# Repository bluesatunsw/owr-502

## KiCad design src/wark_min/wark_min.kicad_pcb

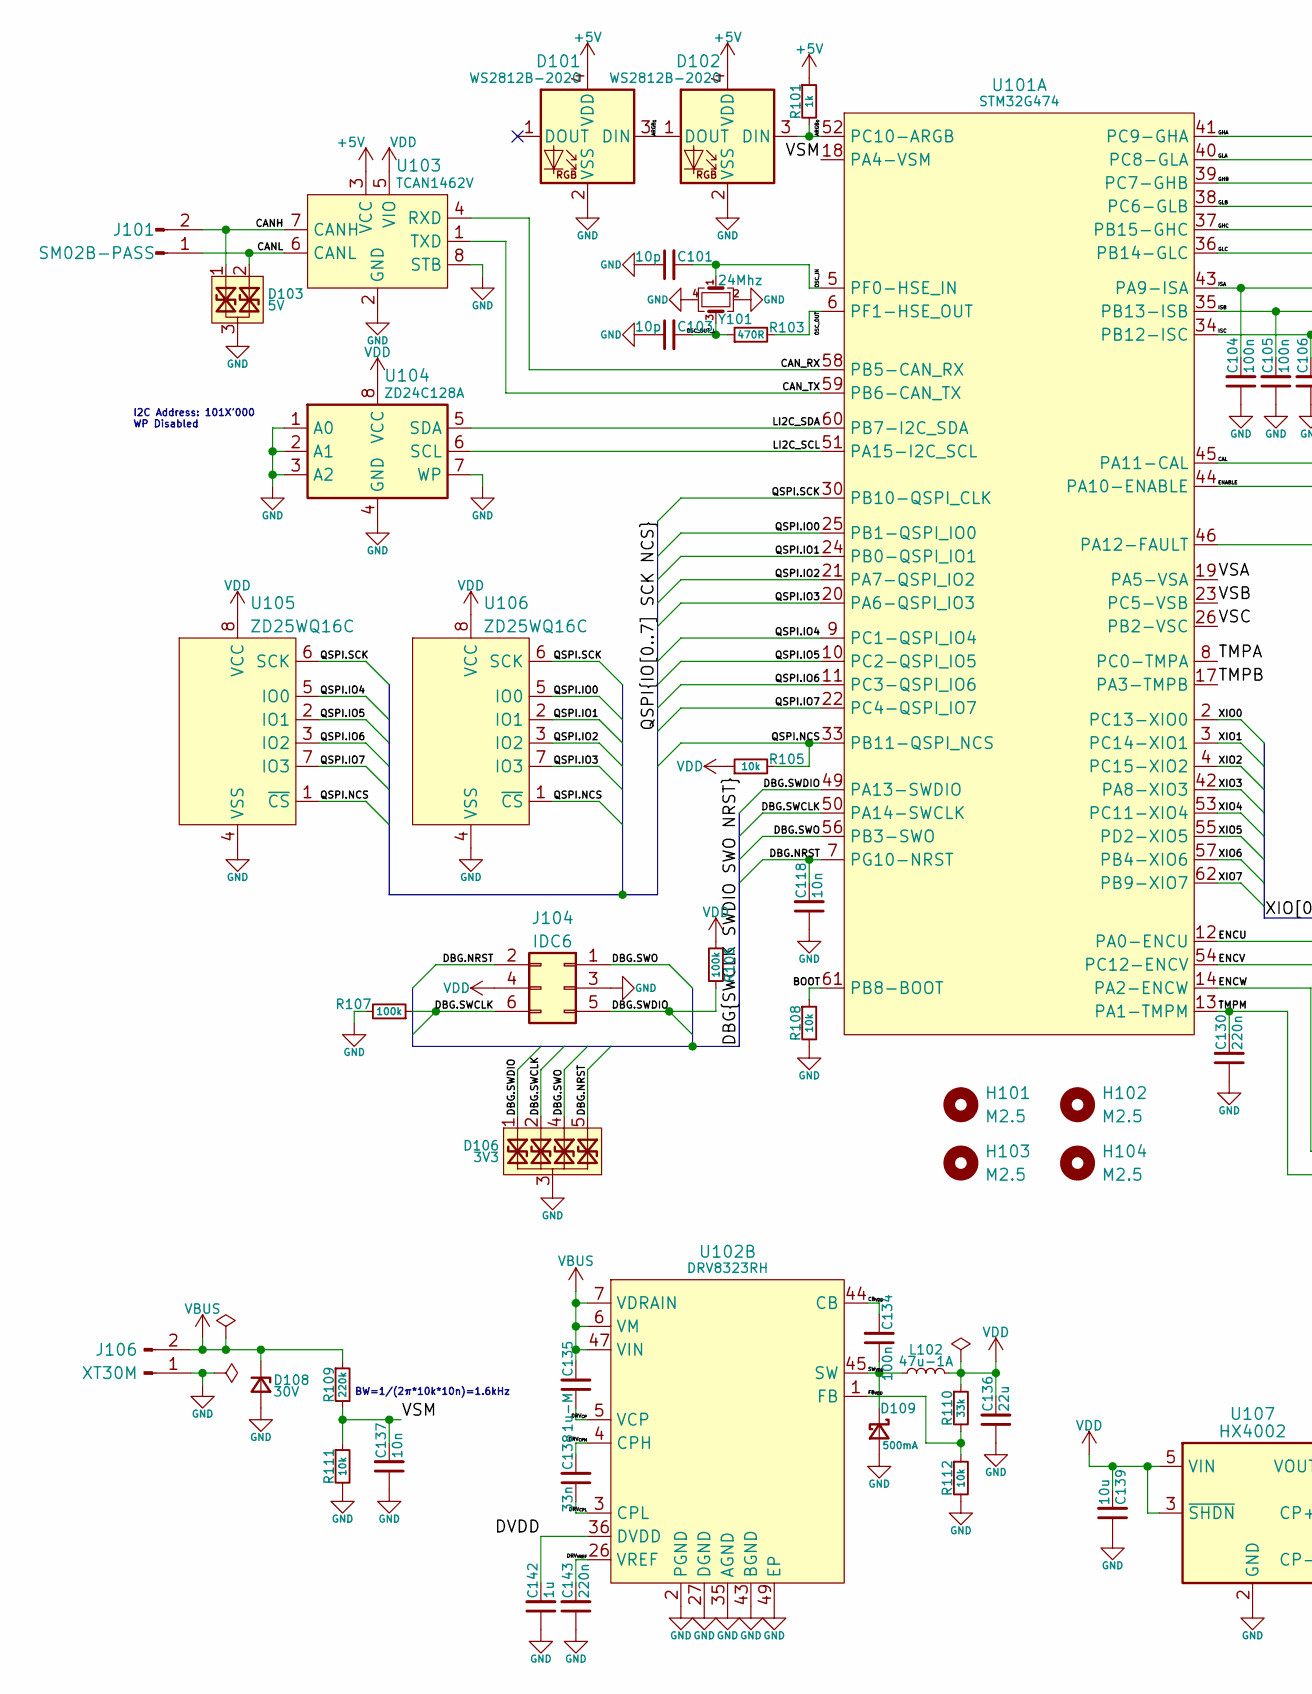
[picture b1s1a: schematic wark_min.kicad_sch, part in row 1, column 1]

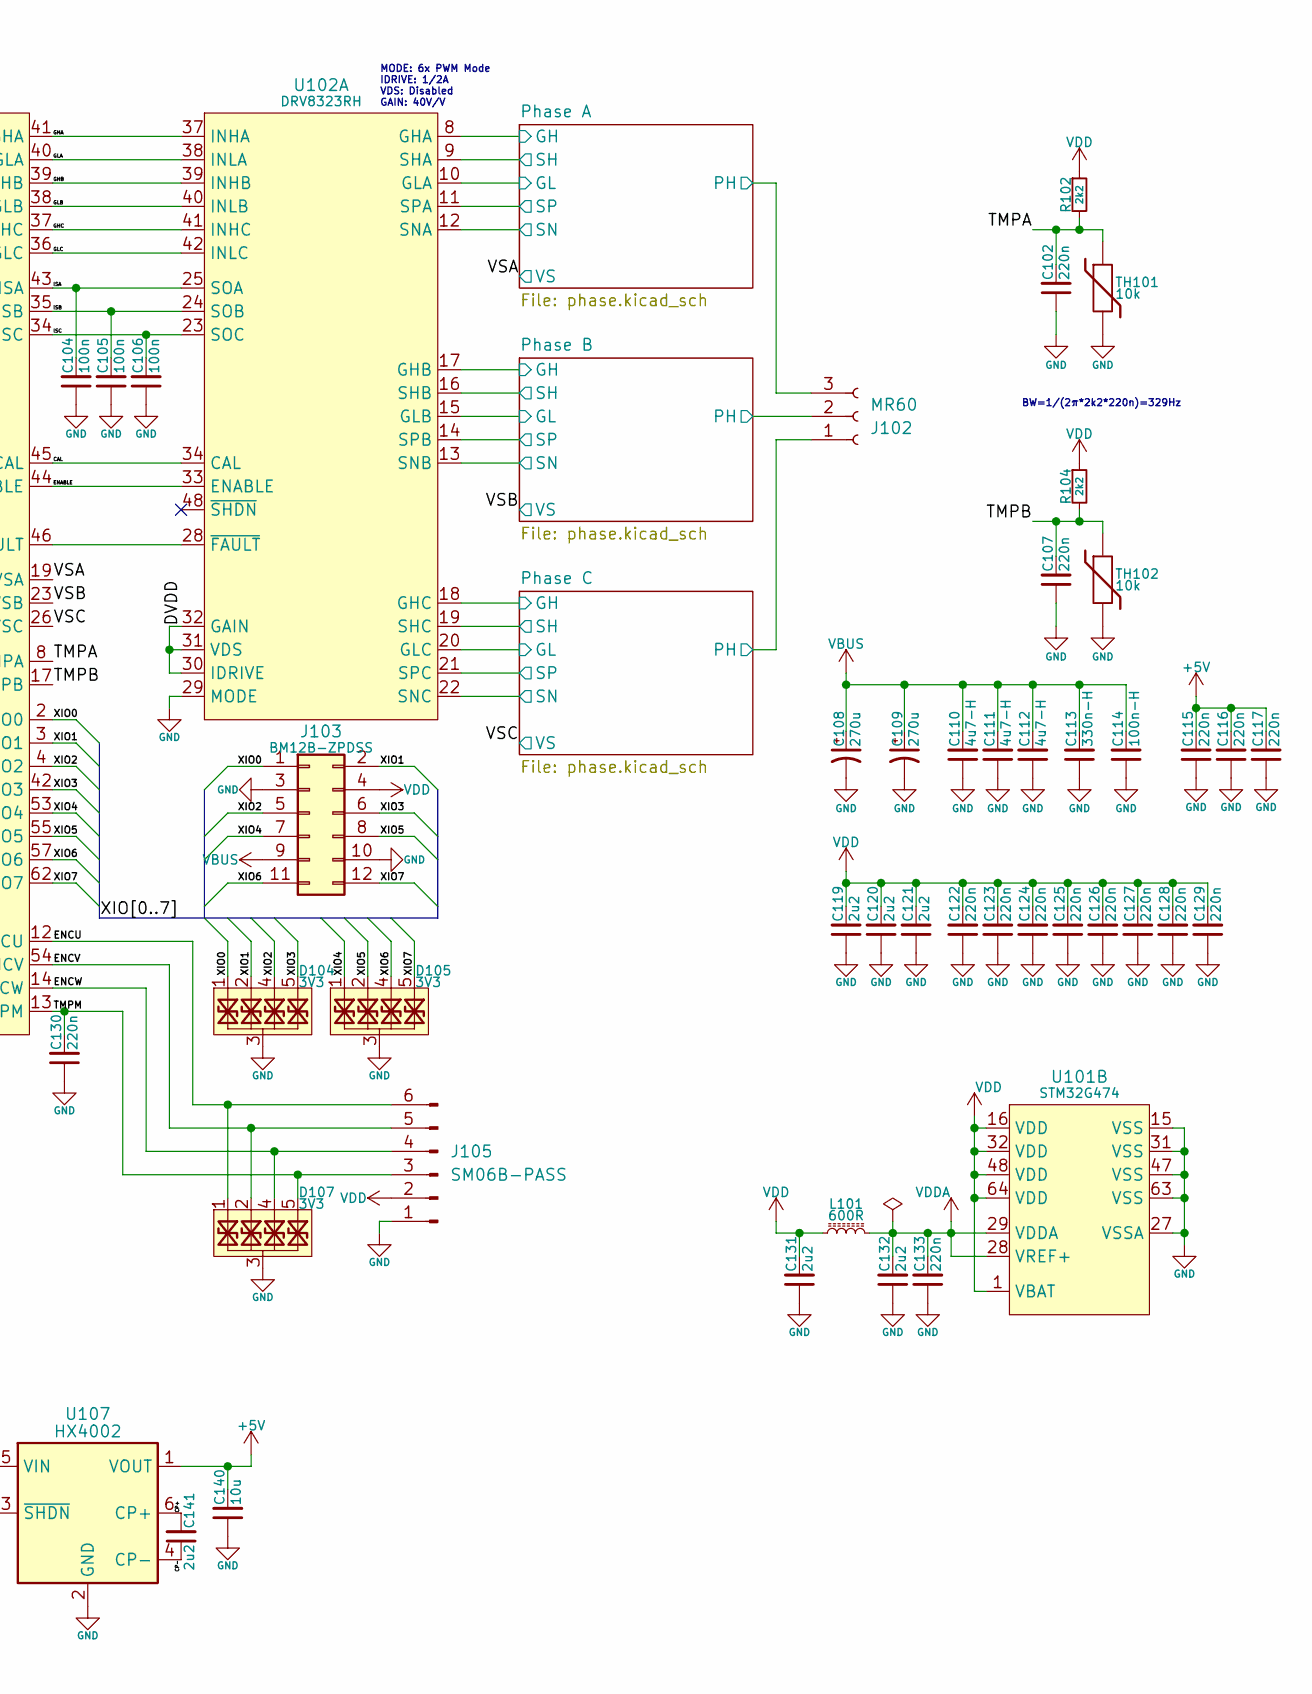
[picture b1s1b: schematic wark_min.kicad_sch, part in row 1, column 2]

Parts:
C101, C103: 10p; C_0402_1005Metric
C102, C107, C115, C116, C117, C122, C123, C124, C125, C126, C127, C128, C129, C130, C133, C143: 220n; C_0402_1005Metric
C104, C105, C106, C134: 100n; C_0402_1005Metric
C108, C109: 270u; CP_Elec_10x10
C110, C111, C112: 4u7-H; C_1210_3225Metric
C113: 330n-H; C_0805_2012Metric
C114: 100n-H; C_0603_1608Metric
C118, C137: 10n; C_0402_1005Metric
C119, C120, C121, C131, C132, C141: 2u2; C_0603_1608Metric
C135: 1u-M; C_0805_2012Metric
C136: 22u; C_1210_3225Metric
C138: 33n; C_0402_1005Metric
C139, C140: 10u; C_1206_3216Metric
C142: 1u; C_0603_1608Metric
D101, D102: WS2812B-2020
D103: 5V; SOT-523
D104, D105, D106, D107: 3V3; UDFN-10_1.35x2.6mm_P0.5mm
D108: 30V; D_SOD-123F
D109: 500mA; D_SOD-123
H101, H102, H103, H104: M2.5
J101: SM02B-PASS; BM02B-PASS
J102: MR60; MR60-F-TopMount
J103: BM12B-ZPDSS
J104: IDC6
J105: SM06B-PASS; BM06B-PASS
J106: XT30M; AMASS_XT30U-M_1x02_P5.0mm_Vertical
L101: 600R; R_0402_1005Metric
L102: 47u-1A; L_Changjiang_FXL0630
R101: 1k; R_0402_1005Metric
R102, R104: 2k2; R_0402_1005Metric
R103: 470R; R_0402_1005Metric
R105, R108, R111, R112: 10k; R_0402_1005Metric
R106, R107: 100k; R_0402_1005Metric
R109: 220k; R_0402_1005Metric
R110: 33k; R_0402_1005Metric
TH101, TH102: 10k; R_0402_1005Metric
U101: STM32G474; LQFP-64-0.5
U102: DRV8323RH; Texas_RGZ0048A_VQFN-48-1EP_7x7mm_P0.5mm_EP5.15x5.15mm
U103: TCAN1462V; SOIC-8_3.9x4.9mm_P1.27mm
U104: ZD24C128A; TSSOP-8_4.4x3.0-0.65
U105, U106: ZD25WQ16C; Winbond_USON-8-1EP_3x2mm_P0.5mm_EP0.2x1.6mm
U107: HX4002; SOT-23-6
Y101: 24Mhz; Crystal_SMD_2016-4Pin_2.0x1.6mm

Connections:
+5V: C115.2, C116.2, C117.2, C140.2, D101.4 (VDD), D102.4 (VDD), R101.1, U103.3 (VCC), U107.1 (VOUT)
/ARGB_{0}: D102.3 (DIN), R101.2, U101.52 (PC10-ARGB)
/ARGB_{1}: D101.3 (DIN), D102.1 (DOUT)
/BOOT: R108.1, U101.61 (PB8-BOOT)
/CAL: U101.45 (PA11-CAL), U102.34 (CAL)
/CANH: D103.1, J101.2, U103.7 (CANH)
/CANL: D103.2, J101.1, U103.6 (CANL)
/CAN_RX: U101.58 (PB5-CAN_RX), U103.4 (RXD)
/CAN_TX: U101.59 (PB6-CAN_TX), U103.1 (TXD)
/CB_{VDD}: C134.2, U102.44 (CB)
/CP+: C141.2, U107.6 (CP+)
/CP-: C141.1, U107.4 (CP-)
/DBG.NRST: C118.2, D106.5, D106.6, J104.2, U101.7 (PG10-NRST)
/DBG.SWCLK: D106.2, D106.9, J104.6, R107.1, U101.50 (PA14-SWCLK)
/DBG.SWDIO: D106.1, D106.10, J104.5, R106.2, U101.49 (PA13-SWDIO)
/DBG.SWO: D106.4, D106.7, J104.1, U101.56 (PB3-SWO)
/DRV_{CPH}: C138.2, U102.4 (CPH)
/DRV_{CPL}: C138.1, U102.3 (CPL)
/DRV_{CP}: C135.1, U102.5 (VCP)
/DRV_{VREF}: C143.2, U102.26 (VREF)
/DVDD: C142.2, U102.30 (IDRIVE), U102.31 (VDS), U102.32 (GAIN), U102.36 (DVDD)
/ENABLE: U101.44 (PA10-ENABLE), U102.33 (ENABLE)
/ENCU: D107.1, D107.10, J105.6, U101.12 (PA0-ENCU)
/ENCV: D107.2, D107.9, J105.5, U101.54 (PC12-ENCV)
/ENCW: D107.4, D107.7, J105.4, U101.14 (PA2-ENCW)
/FB_{VDD}: R110.2, R112.1, U102.1 (FB)
/GHA: U101.41 (PC9-GHA), U102.37 (INHA)
/GHB: U101.39 (PC7-GHB), U102.39 (INHB)
/GHC: U101.37 (PB15-GHC), U102.41 (INHC)
/GLA: U101.40 (PC8-GLA), U102.38 (INLA)
/GLB: U101.38 (PC6-GLB), U102.40 (INLB)
/GLC: U101.36 (PB14-GLC), U102.42 (INLC)
/ISA: C104.2, U101.43 (PA9-ISA), U102.25 (SOA)
/ISB: C105.2, U101.35 (PB13-ISB), U102.24 (SOB)
/ISC: C106.2, U101.34 (PB12-ISC), U102.23 (SOC)
/LI2C_SCL: U101.51 (PA15-I2C_SCL), U104.6 (SCL)
/LI2C_SDA: U101.60 (PB7-I2C_SDA), U104.5 (SDA)
/OSC_IN: C101.2, U101.5 (PF0-HSE_IN), Y101.1
/OSC_OUT: R103.2, U101.6 (PF1-HSE_OUT)
/OSC_OUT_L: C103.2, R103.1, Y101.3
/Phase A/GH: U102.8 (GHA); also elsewhere on the board
/Phase A/GL: U102.10 (GLA); also elsewhere on the board
/Phase A/PH: J102.3, U102.9 (SHA); also elsewhere on the board
/Phase A/SP: U102.11 (SPA); also elsewhere on the board
/Phase B/GH: U102.17 (GHB); also elsewhere on the board
/Phase B/GL: U102.15 (GLB); also elsewhere on the board
/Phase B/PH: J102.2, U102.16 (SHB); also elsewhere on the board
/Phase B/SP: U102.14 (SPB); also elsewhere on the board
/Phase C/GH: U102.18 (GHC); also elsewhere on the board
/Phase C/GL: U102.20 (GLC); also elsewhere on the board
/Phase C/PH: J102.1, U102.19 (SHC); also elsewhere on the board
/Phase C/SP: U102.21 (SPC); also elsewhere on the board
/QSPI.IO0: U101.25 (PB1-QSPI_IO0), U106.5 (IO0)
/QSPI.IO1: U101.24 (PB0-QSPI_IO1), U106.2 (IO1)
/QSPI.IO2: U101.21 (PA7-QSPI_IO2), U106.3 (IO2)
/QSPI.IO3: U101.20 (PA6-QSPI_IO3), U106.7 (IO3)
/QSPI.IO4: U101.9 (PC1-QSPI_IO4), U105.5 (IO0)
/QSPI.IO5: U101.10 (PC2-QSPI_IO5), U105.2 (IO1)
/QSPI.IO6: U101.11 (PC3-QSPI_IO6), U105.3 (IO2)
/QSPI.IO7: U101.22 (PC4-QSPI_IO7), U105.7 (IO3)
/QSPI.NCS: R105.2, U101.33 (PB11-QSPI_NCS), U105.1 (~CS), U106.1 (~CS)
/QSPI.SCK: U101.30 (PB10-QSPI_CLK), U105.6 (SCK), U106.6 (SCK)
/SW_{VDD}: C134.1, D109.1 (K), L102.1, U102.45 (SW)
/TMPA: C102.2, R102.2, TH101.1, U101.8 (PC0-TMPA)
/TMPB: C107.2, R104.2, TH102.1, U101.17 (PA3-TMPB)
/TMPM: C130.2, D107.5, D107.6, J105.3, U101.13 (PA1-TMPM)
/VSA: U101.19 (PA5-VSA); also elsewhere on the board
/VSB: U101.23 (PC5-VSB); also elsewhere on the board
/VSC: U101.26 (PB2-VSC); also elsewhere on the board
/VSM: C137.2, R109.2, R111.1, U101.18 (PA4-VSM)
/XIO0: D104.1, D104.10, J103.1, U101.2 (PC13-XIO0)
/XIO1: D104.2, D104.9, J103.2, U101.3 (PC14-XIO1)
/XIO2: D104.4, D104.7, J103.5, U101.4 (PC15-XIO2)
/XIO3: D104.5, D104.6, J103.6, U101.42 (PA8-XIO3)
/XIO4: D105.1, D105.10, J103.7, U101.53 (PC11-XIO4)
/XIO5: D105.2, D105.9, J103.8, U101.55 (PD2-XIO5)
/XIO6: D105.4, D105.7, J103.11, U101.57 (PB4-XIO6)
/XIO7: D105.5, D105.6, J103.12, U101.62 (PB9-XIO7)
GND: C101.1, C102.1, C103.1, C104.1, C105.1, C106.1, C107.1, C108.2, C109.2, C110.1, C111.1, C112.1, C113.1, C114.1, C115.1, C116.1, C117.1, C118.1, C119.1, C120.1, C121.1, C122.1, C123.1, C124.1, C125.1, C126.1, C127.1, C128.1, C129.1, C130.1, C131.1, C132.1, C133.1, C136.1, C137.1, C139.1, C140.1, C142.1, C143.1, D101.2 (VSS), D102.2 (VSS), D103.3, D104.3, D104.8, D105.3, D105.8, D106.3, D106.8, D107.3, D107.8, D108.2 (A), D109.2 (A), J103.3, J103.10, J104.3, J105.1, J106.1, R107.2, R108.2, R111.2, R112.2, TH101.2, TH102.2, U101.15 (VSS), U101.27 (VSSA), U101.31 (VSS), U101.47 (VSS), U101.63 (VSS), U102.2 (PGND), U102.12 (SNA), U102.13 (SNB), U102.22 (SNC), U102.27 (DGND), U102.29 (MODE), U102.35 (AGND), U102.43 (BGND), U102.49 (EP), U103.2 (GND), U103.8 (STB), U103.9 (EP), U104.1 (A0), U104.2 (A1), U104.3 (A2), U104.4 (GND), U104.7 (WP), U105.4 (VSS), U106.4 (VSS), U107.2 (GND), Y101.2, Y101.4; also elsewhere on the board
unnamed: U101.46 (PA12-FAULT), U102.28 (~FAULT)
VBUS: C108.1, C109.1, C110.2, C111.2, C112.2, C113.2, C114.2, C135.2, D108.1 (K), J103.9, J106.2, R109.1, U102.6 (VM), U102.7 (VDRAIN), U102.47 (VIN); also elsewhere on the board
VDD: C119.2, C120.2, C121.2, C122.2, C123.2, C124.2, C125.2, C126.2, C127.2, C128.2, C129.2, C131.2, C136.2, C139.2, J103.4, J104.4, J105.2, L101.1, L102.2, R102.1, R104.1, R105.1, R106.1, R110.1, U101.1 (VBAT), U101.16 (VDD), U101.32 (VDD), U101.48 (VDD), U101.64 (VDD), U103.5 (VIO), U104.8 (VCC), U105.8 (VCC), U106.8 (VCC), U107.3 (~SHDN), U107.5 (VIN)
VDDA: C132.2, C133.2, L101.2, U101.28 (VREF+), U101.29 (VDDA)

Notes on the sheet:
I2C Address: 101X'000 WP Disabled
BW=1/(2π*2k2*220n)=329Hz
MODE: 6x PWM Mode IDRIVE: 1/2A VDS: Disabled GAIN: 40V/V
BW=1/(2π*10k*10n)=1.6kHz

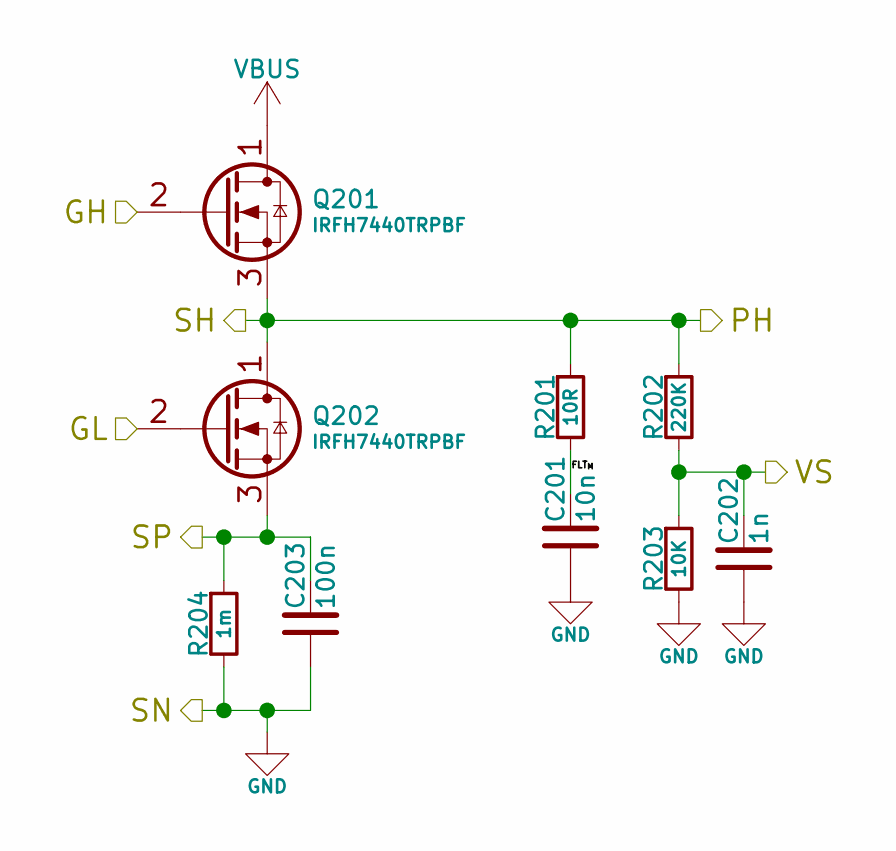
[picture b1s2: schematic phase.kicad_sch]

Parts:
C201: 10n; C_0402_1005Metric
C202: 1n; C_0402_1005Metric
C203: 100n; C_0402_1005Metric
Q201, Q202: IRFH7440TRPBF; PQFN_5x6mm_E_DGS
R201: 10R; R_0402_1005Metric
R202: 220K; R_0402_1005Metric
R203: 10K; R_0402_1005Metric
R204: 1m; R_2512_6332Metric

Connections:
/Phase A/FLT_{M}: C201.2, R201.2
/Phase A/GH: Q201.2 (G); also elsewhere on the board
/Phase A/GL: Q202.2 (G); also elsewhere on the board
/Phase A/PH: Q201.3 (S), Q202.1 (D), R201.1, R202.1; also elsewhere on the board
/Phase A/SP: C203.2, Q202.3 (S), R204.1; also elsewhere on the board
/VSA: C202.2, R202.2, R203.1; also elsewhere on the board
GND: C201.1, C202.1, C203.1, R203.2, R204.2; also elsewhere on the board
VBUS: Q201.1 (D); also elsewhere on the board

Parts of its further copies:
C301, C401: 10n; C_0402_1005Metric
C302, C402: 1n; C_0402_1005Metric
C303, C403: 100n; C_0402_1005Metric
Q301, Q302, Q401, Q402: IRFH7440TRPBF; PQFN_5x6mm_E_DGS
R301, R401: 10R; R_0402_1005Metric
R302, R402: 220K; R_0402_1005Metric
R303, R403: 10K; R_0402_1005Metric
R304, R404: 1m; R_2512_6332Metric

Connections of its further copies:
/Phase B/FLT_{M}: C301.2, R301.2
/Phase B/GH: Q301.2 (G); also elsewhere on the board
/Phase B/GL: Q302.2 (G); also elsewhere on the board
/Phase B/PH: Q301.3 (S), Q302.1 (D), R301.1, R302.1; also elsewhere on the board
/Phase B/SP: C303.2, Q302.3 (S), R304.1; also elsewhere on the board
/Phase C/FLT_{M}: C401.2, R401.2
/Phase C/GH: Q401.2 (G); also elsewhere on the board
/Phase C/GL: Q402.2 (G); also elsewhere on the board
/Phase C/PH: Q401.3 (S), Q402.1 (D), R401.1, R402.1; also elsewhere on the board
/Phase C/SP: C403.2, Q402.3 (S), R404.1; also elsewhere on the board
/VSB: C302.2, R302.2, R303.1; also elsewhere on the board
/VSC: C402.2, R402.2, R403.1; also elsewhere on the board
GND: C301.1, C302.1, C303.1, C401.1, C402.1, C403.1, R303.2, R304.2, R403.2, R404.2; also elsewhere on the board
VBUS: Q301.1 (D), Q401.1 (D); also elsewhere on the board

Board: 6 copper layers, 113 parts (96 on the bottom side), 86 nets, no tracks yet.
